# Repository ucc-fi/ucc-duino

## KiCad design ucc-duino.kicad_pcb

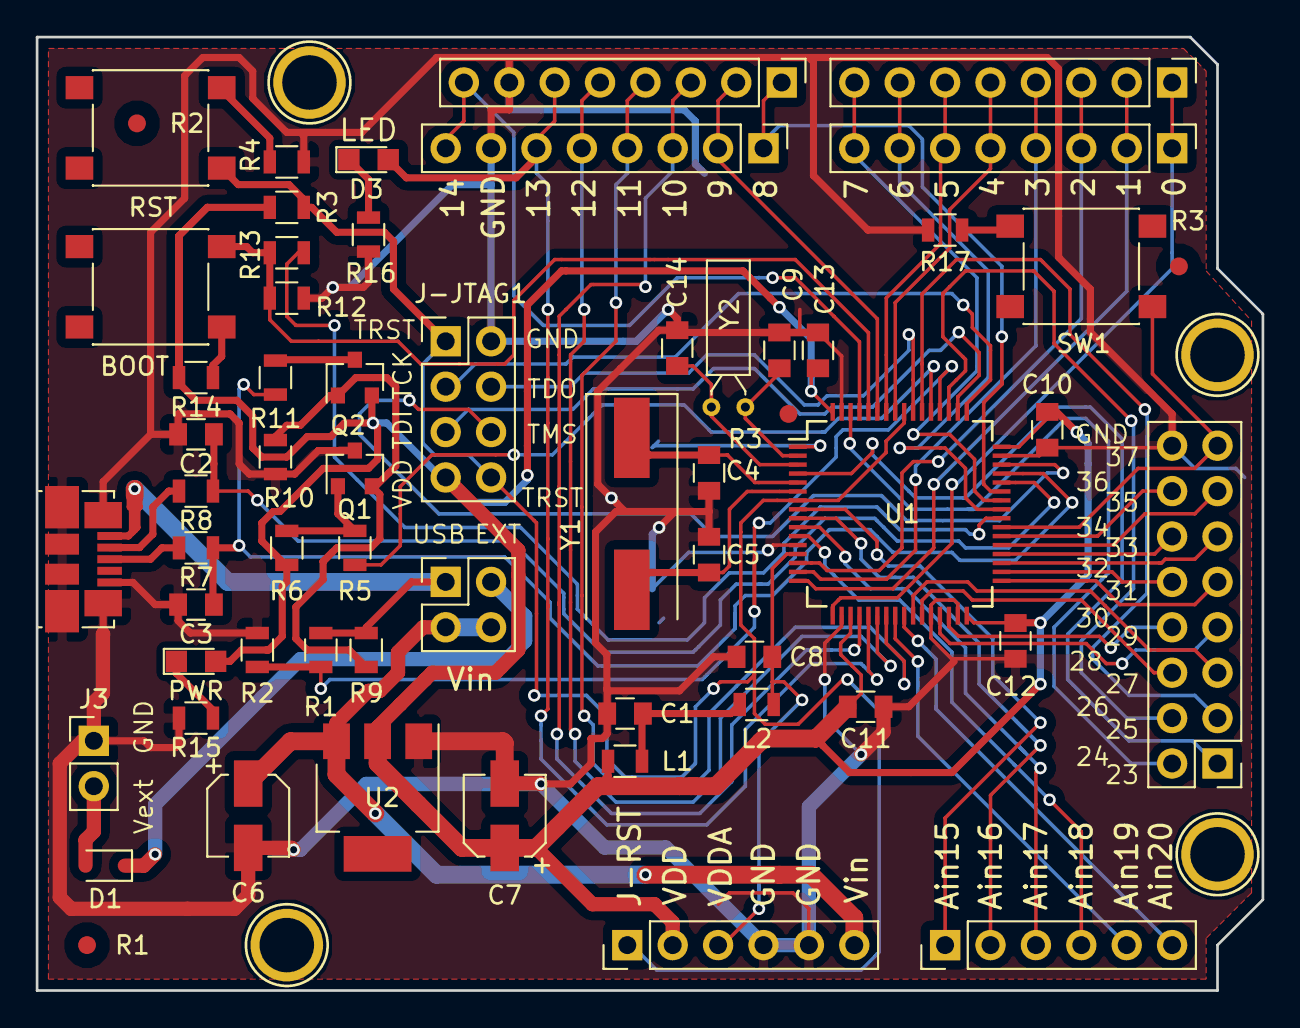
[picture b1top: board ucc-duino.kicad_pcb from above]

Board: 2 copper layers, 68.6 x 53.3 mm, 56 parts (1 on the bottom side), 33 nets.

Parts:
BOOT: SW_Push; SW_SPST_PTS645
BT1: Battery_Cell; Keystone_3000_1x12mm-CoinCell
C1, C8, C9, C10, C11, C12: 1uF; C_0805
C2, C3: 47pF; C_0805
C4, C5, C14: ?pF; C_0805
C6, C7: 22uF; CP_Elec_4x5.8
C13: ?Pf; C_0805
D1: D; D_SOD-323F
D3: LED_USR; LED_0805
J3: Con1x2F; Pin_Header_Straight_1x02_Pitch2.54mm
J-JTAG1: Con2x4Odd; Pin_Header_Straight_2x04_Pitch2.54mm
L1, L2: 2kH; L_0805
P5, P6, P7, P8: CONN_01X01; Arduino_1pin
PWR: LED_PWR; LED_0805
Q1, Q2: BC817; SOT-23
R1, R2#2: 1.5k; R_0805
R1#2, R2, R3, R3#2: Fiducial_1mm_Dia_2.54mm_Outer_CopperTop
R3#3, R12: 10k; R_0805
R4, R13, R14, R17: 1k; R_0805
R5: 1K; R_0805
R6: 47K; R_0805
R7, R8: 22; R_0805
R9: 10K; R_0805
R10: 36K; R_0805
R11: 1.5K; R_0805
R15, R16: 110; R_0805
RST: SW_Push; SW_SPST_PTS645
SW1: SW_USR; SW_SPST_PTS645
U1: STM32F103R4T6; LQFP-64_10x10mm_Pitch0.5mm
U2: AP1117-33; SOT-223
Y1: OSC 8MHz; Crystal_SMD_HC49-SD
Y2: OSC 32768KHz; Crystal_DS26_d2.0mm_l6.0mm_Horizontal

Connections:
/13: D3.2, U1.21
/21: C13.2, U1.2, Y2.1
/22: C14.2, U1.3, Y2.2
/37: SW1.2, U1.39
/BOOT0: BOOT.1, R12.1, R13.1, U1.60
/DISC: R5.2, U1.53
/JTAG-TCK: J-JTAG1.3, U1.49
/JTAG-TDI: J-JTAG1.5, U1.50
/JTAG-TDO: J-JTAG1.4, U1.55
/JTAG-TMS: J-JTAG1.6, U1.46
/JTAG-TRST: J-JTAG1.1, J-JTAG1.8, R3#3.2, RST.2, U1.7, U1.56
/OSC1: C4.2, U1.5, Y1.1
/OSC2: C5.2, U1.6, Y1.2
/USB_P: R1.2, R2#2.1, U1.52
/VBAT: BT1.1, U1.1
/Vin: C6.1, U2.3
GND: BT1.2, C1.2, C2.2, C3.2, C4.1, C5.1, C6.2, C7.2, C8.2, C9.2, C10.2, C11.2, C12.2, C13.1, C14.1, J3.1, J-JTAG1.2, Q1.3, R2#2.2, R4.2, R10.1, R12.2, R15.2, R16.2, R17.2, U1.12, U1.18, U1.28, U1.31, U1.47, U1.63, U2.1
unnamed: C1.1, L1.2, L2.1
unnamed: C2.1, R8.1, U1.44
unnamed: C3.1, R7.1, R11.1, U1.45
unnamed: D1.2, J3.2
unnamed: PWR.1, R15.1
unnamed: D3.1, R16.1
unnamed: Q1.1, R5.1, R6.2
unnamed: Q1.2, Q2.1, R9.1, R10.2
unnamed: Q2.3, R11.2
unnamed: R4.1, RST.1
unnamed: R13.2, U1.40
unnamed: BOOT.2, R14.2
unnamed: R17.1, SW1.1
VBUS: R1.1, R9.2
VDD: C7.1, C9.1, C10.1, C11.1, C12.1, J-JTAG1.7, L1.1, PWR.2, Q2.2, R3#3.1, R6.1, R14.1, U1.19, U1.32, U1.48, U1.64, U2.2
VDDA: C8.1, L2.2, U1.13

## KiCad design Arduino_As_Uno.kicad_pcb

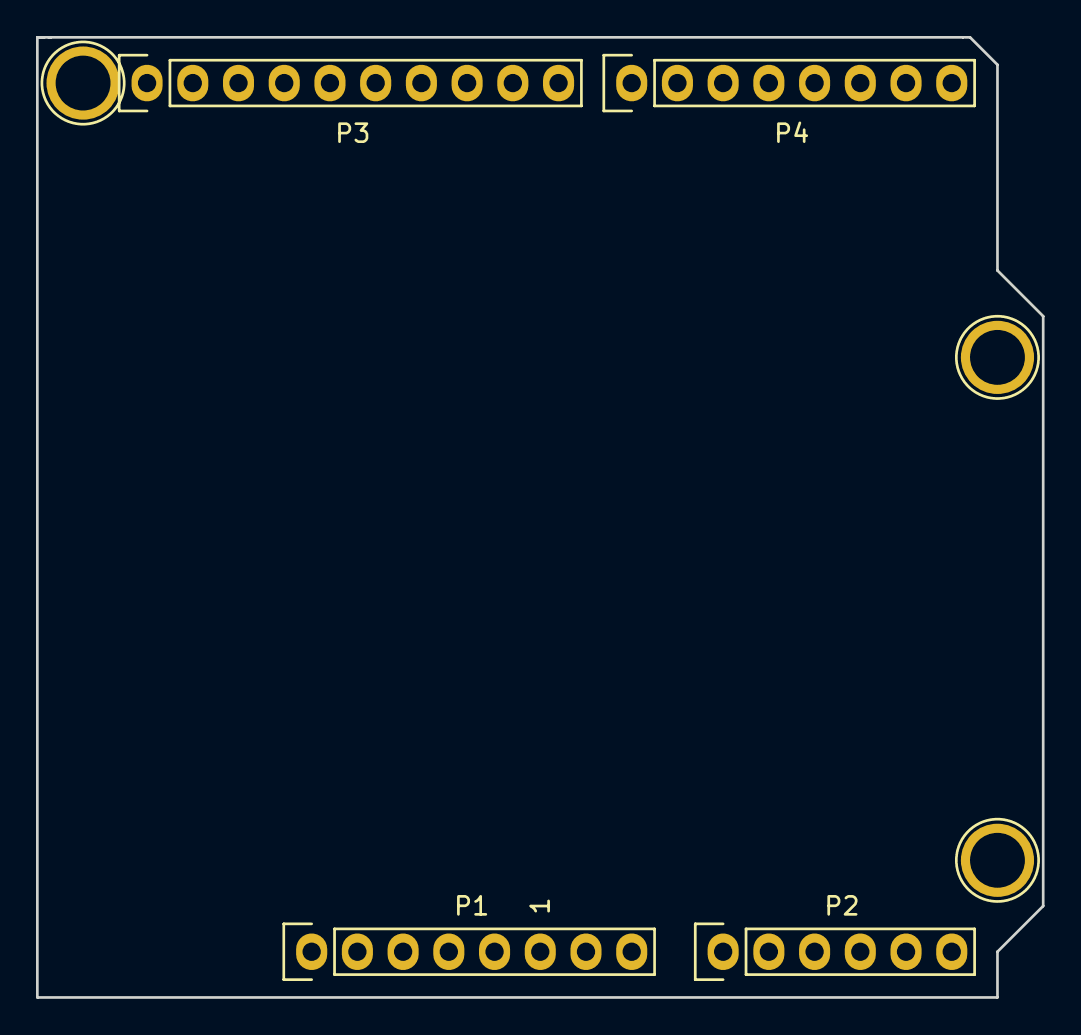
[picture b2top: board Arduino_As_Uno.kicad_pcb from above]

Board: 2 copper layers, 55.9 x 53.3 mm, 7 parts (0 on the bottom side), 3 nets, no tracks yet.

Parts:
P1: Power; Socket_Strip_Arduino_1x08
P2: Analog; Socket_Strip_Arduino_1x06
P3: Digital; Socket_Strip_Arduino_1x10
P4: Digital; Socket_Strip_Arduino_1x08
P6, P7, P8: CONN_01X01; Arduino_1pin

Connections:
/A4(SDA): P2.5, P3.2
/A5(SCL): P2.6, P3.1
GND: P1.6, P1.7, P3.4

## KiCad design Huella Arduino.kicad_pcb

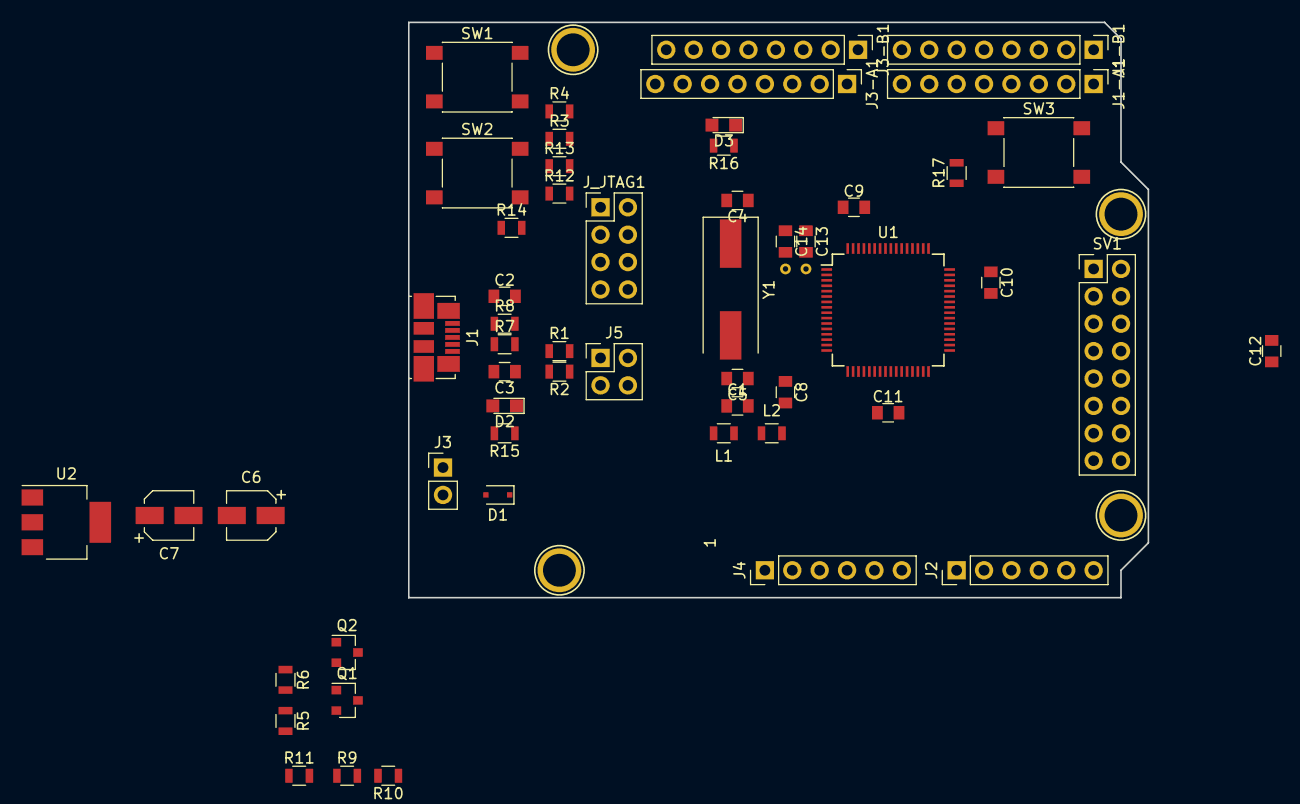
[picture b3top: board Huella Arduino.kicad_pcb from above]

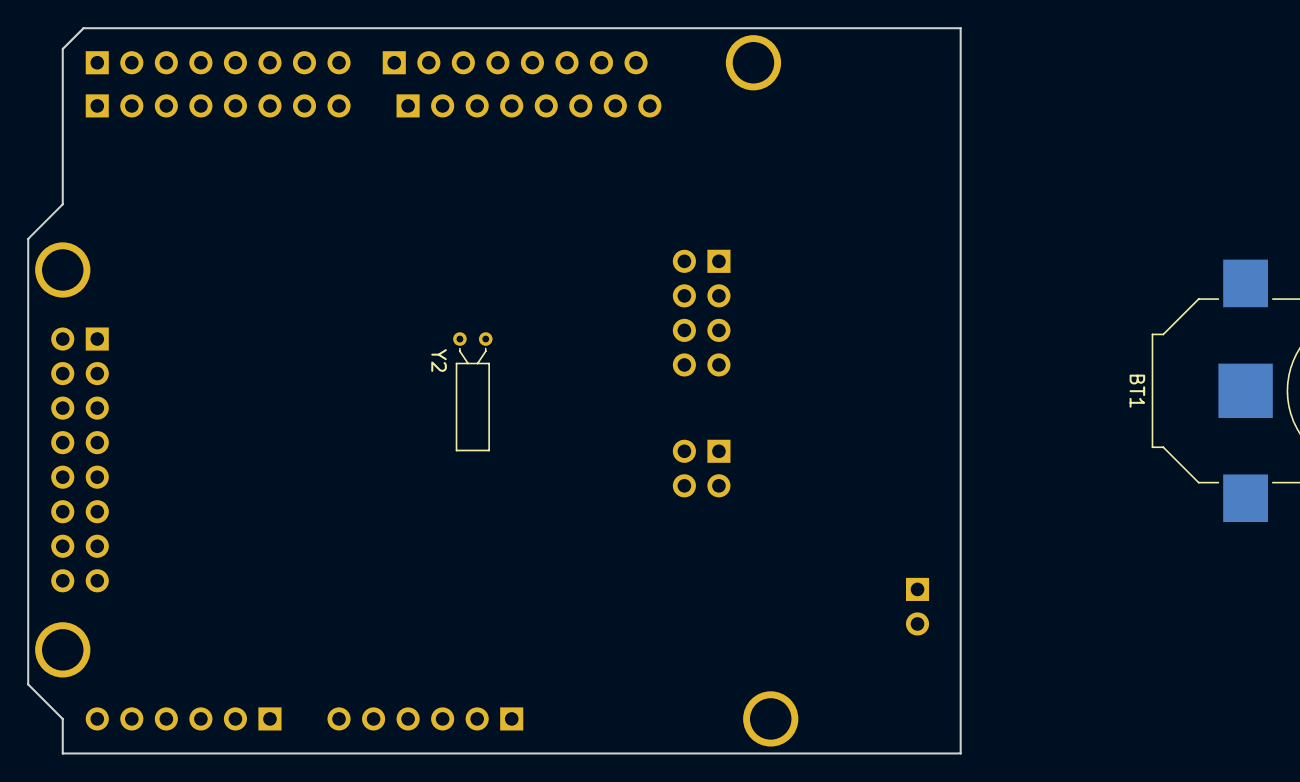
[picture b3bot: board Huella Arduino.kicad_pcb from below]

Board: 2 copper layers, 68.6 x 53.3 mm, 61 parts (2 on the bottom side), 70 nets, no tracks yet.

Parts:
BT1: Battery_Cell; Keystone_3000_1x12mm-CoinCell
C1, C8, C9, C10, C11, C12: 1uF; C_0805
C2, C3: 47pF; C_0805
C4, C5, C14: ?pF; C_0805
C6, C7: 22uF; CP_Elec_4x5.8
C13: ?Pf; C_0805
D1: D; D_SOD-323F
D2: LED_PWR; LED_0805
D3: LED_USR; LED_0805
J1: USB_OTG; USB_Micro-B_Molex_47346-0001
J1-A1, J1-B1, J3-A1, J3-B1: Con1x8F; Pin_Header_Straight_1x08_Pitch2.54mm
J2, J4: Con1x6F; Pin_Header_Straight_1x06_Pitch2.54mm
J3: Con1x2F; Pin_Header_Straight_1x02_Pitch2.54mm
J5: Con2x2CClocw; Pin_Header_Straight_2x02_Pitch2.54mm
J_JTAG1: Con2x4CCw; Pin_Header_Straight_2x04_Pitch2.54mm
L1, L2: 2kH; L_0805
P5, P6, P7, P8: CONN_01X01; Arduino_1pin
Q1, Q2: BC817; SOT-23
R1, R2: 1.5k; R_0805
R3, R12: 10k; R_0805
R4, R13, R14, R17: 1k; R_0805
R5: 1K; R_0805
R6: 47K; R_0805
R7, R8: 22; R_0805
R9: 10K; R_0805
R10: 36K; R_0805
R11: 1.5K; R_0805
R15, R16: 110; R_0805
SV1: Con2x8CCw; Pin_Header_Straight_2x08_Pitch2.54mm
SW1, SW2: SW_Push; SW_SPST_PTS645
SW3: SW_USR; SW_SPST_PTS645
U1: STM32F103R4T6; LQFP-64_10x10mm_Pitch0.5mm
U2: AP1117-33; SOT-223
Y1: OSC 8MHz; Crystal_SMD_HC49-SD
Y2: OSC 32768KHz; Crystal_DS26_d2.0mm_l6.0mm_Horizontal

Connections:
/0: J1-A1.1, J1-B1.1, U1.17
/1: J1-A1.2, J1-B1.2, U1.16
/2: J1-A1.3, J1-B1.3, U1.14
/3: J1-A1.4, J1-B1.4, U1.15
/4: J1-A1.5, J1-B1.5, U1.57
/5: J1-A1.6, J1-B1.6, U1.58
/6: J1-A1.7, J1-B1.7, U1.41
/7: J1-A1.8, J1-B1.8, U1.42
/8: J3-A1.1, J3-B1.1, U1.43
/9: J3-A1.2, J3-B1.2, U1.59
/10: J3-A1.3, J3-B1.3, U1.20
/11: J3-A1.4, J3-B1.4, U1.23
/12: J3-A1.5, J3-B1.5, U1.22
/13: D3.2, J3-A1.6, J3-B1.6, U1.21
/14: J3-A1.8, J3-B1.8, U1.61
/15: J2.1, U1.8
/16: J2.2, U1.9
/17: J2.3, U1.10
/18: J2.4, U1.11
/19: J2.5, U1.24
/20: J2.6, U1.25
/21: C13.2, U1.2, Y2.1
/22: C14.2, U1.3, Y2.2
/23: SV1.9, U1.4
/24: SV1.8, U1.62
/25: SV1.10, U1.54
/26: SV1.7, U1.51
/27: SV1.11, U1.26
/28: SV1.6, U1.27
/29: SV1.12, U1.29
/30: SV1.5, U1.30
/31: SV1.13, U1.33
/32: SV1.4, U1.34
/33: SV1.14, U1.35
/34: SV1.3, U1.36
/35: SV1.15, U1.37
/36: SV1.2, U1.38
/37: SV1.16, SW3.2, U1.39
/BOOT0: R12.1, R13.1, SW2.1, U1.60
/DISC: R5.2, U1.53
/JTAG-TCK: J_JTAG1.6, U1.49
/JTAG-TDI: J_JTAG1.7, U1.50
/JTAG-TDO: J_JTAG1.3, U1.55
/JTAG-TMS: J_JTAG1.2, U1.46
/JTAG-TRST: J4.1, J_JTAG1.1, J_JTAG1.5, R3.2, SW1.2, U1.7, U1.56
/OSC1: C4.2, U1.5, Y1.1
/OSC2: C5.2, U1.6, Y1.2
/USB_P: R1.2, R2.1, U1.52
/VBAT: BT1.1, U1.1
/VDDA: C8.1, L2.2, U1.13
/Vin: C6.1, J4.6, J5.3, J5.4, U2.3
GND: BT1.2, C1.2, C2.2, C3.2, C4.1, C5.1, C6.2, C7.2, C8.2, C9.2, C10.2, C11.2, C12.2, C13.1, C14.1, J1.5, J1.6, J3.1, J3-A1.7, J3-B1.7, J4.4, J4.5, J_JTAG1.4, Q1.3, R2.2, R4.2, R10.1, R12.2, R15.2, R16.2, R17.2, SV1.1, U1.12, U1.18, U1.28, U1.31, U1.47, U1.63, U2.1
unnamed: C1.1, L1.2, L2.1
unnamed: C2.1, R8.1, U1.44
unnamed: C3.1, R7.1, R11.1, U1.45
unnamed: D1.1, J5.2
unnamed: D1.2, J3.2
unnamed: D2.1, R15.1
unnamed: D3.1, R16.1
unnamed: J1.2, R8.2
unnamed: J1.3, R7.2
unnamed: Q1.1, R5.1, R6.2
unnamed: Q1.2, Q2.1, R9.1, R10.2
unnamed: Q2.3, R11.2
unnamed: R4.1, SW1.1
unnamed: R13.2, U1.40
unnamed: R14.2, SW2.2
unnamed: R17.1, SW3.1
VBUS: J1.1, J5.1, R1.1, R9.2
VDD: C7.1, C9.1, C10.1, C11.1, C12.1, D2.2, J4.2, J4.3, J_JTAG1.8, L1.1, Q2.2, R3.1, R6.1, R14.1, U1.19, U1.32, U1.48, U1.64, U2.2

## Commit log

2018-04-27 Se creo proyecto y se agrego circuito de USB
2018-04-27 versión del viernes
    le agregué borneras, etiquetas, regulador, etc.
    falta masas y alimentación distribuída al chip
2018-05-02 Agregado filtro LCLC en VDDA
2018-05-02 agregué librería STMangosto
2018-05-02 Bornera SV1 + Jtag
2018-05-02 casi terminada
2018-05-02 Fin esquemático, asignación de encapsulados casi lista
2018-05-03 faltan asignar ferrites/bobinas sw y ocs
2018-05-04 Posicionado inicial de componentes en placa
2018-05-04 faltaba guardar algo
2018-05-07 Quité archivos innecesarios
2018-06-01 Primeras pistas y leve reacomodación de componentes
2018-06-07 Pistas day 3
2018-06-08 Day4
2018-06-13 8 pistas to go
2018-06-15 Fin de ruteo
    faltan fiduciarios y texto
2018-06-18 Lista para revisión1
2018-06-18 Algunos retoques
2018-07-19 BOM y valores de componentes
2018-07-19 bom 2
